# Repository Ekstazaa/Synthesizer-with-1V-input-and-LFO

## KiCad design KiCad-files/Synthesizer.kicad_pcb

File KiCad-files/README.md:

## KiCad Design Files

This folder contains the KiCad design files for the analog synthesizer PCB.

### File descriptions

- **Synthesizer.kicad_sch**  
  KiCad schematic file containing the complete circuit design, including the VCO, exponential converter, summing amplifier, LFO, and supporting circuitry.

- **Synthesizer.kicad_pcb**  
  KiCad PCB layout file defining the board outline, component placement, routing, and copper layers.

- **Synthesizer.kicad_pro**  
  KiCad project file that links the schematic and PCB layout and stores project-specific settings.

- **Synthesizer_fab_file_11_01_26.zip**  
  Fabrication files exported from KiCad, including Gerber files and drill data, ready for PCB manufacturing.

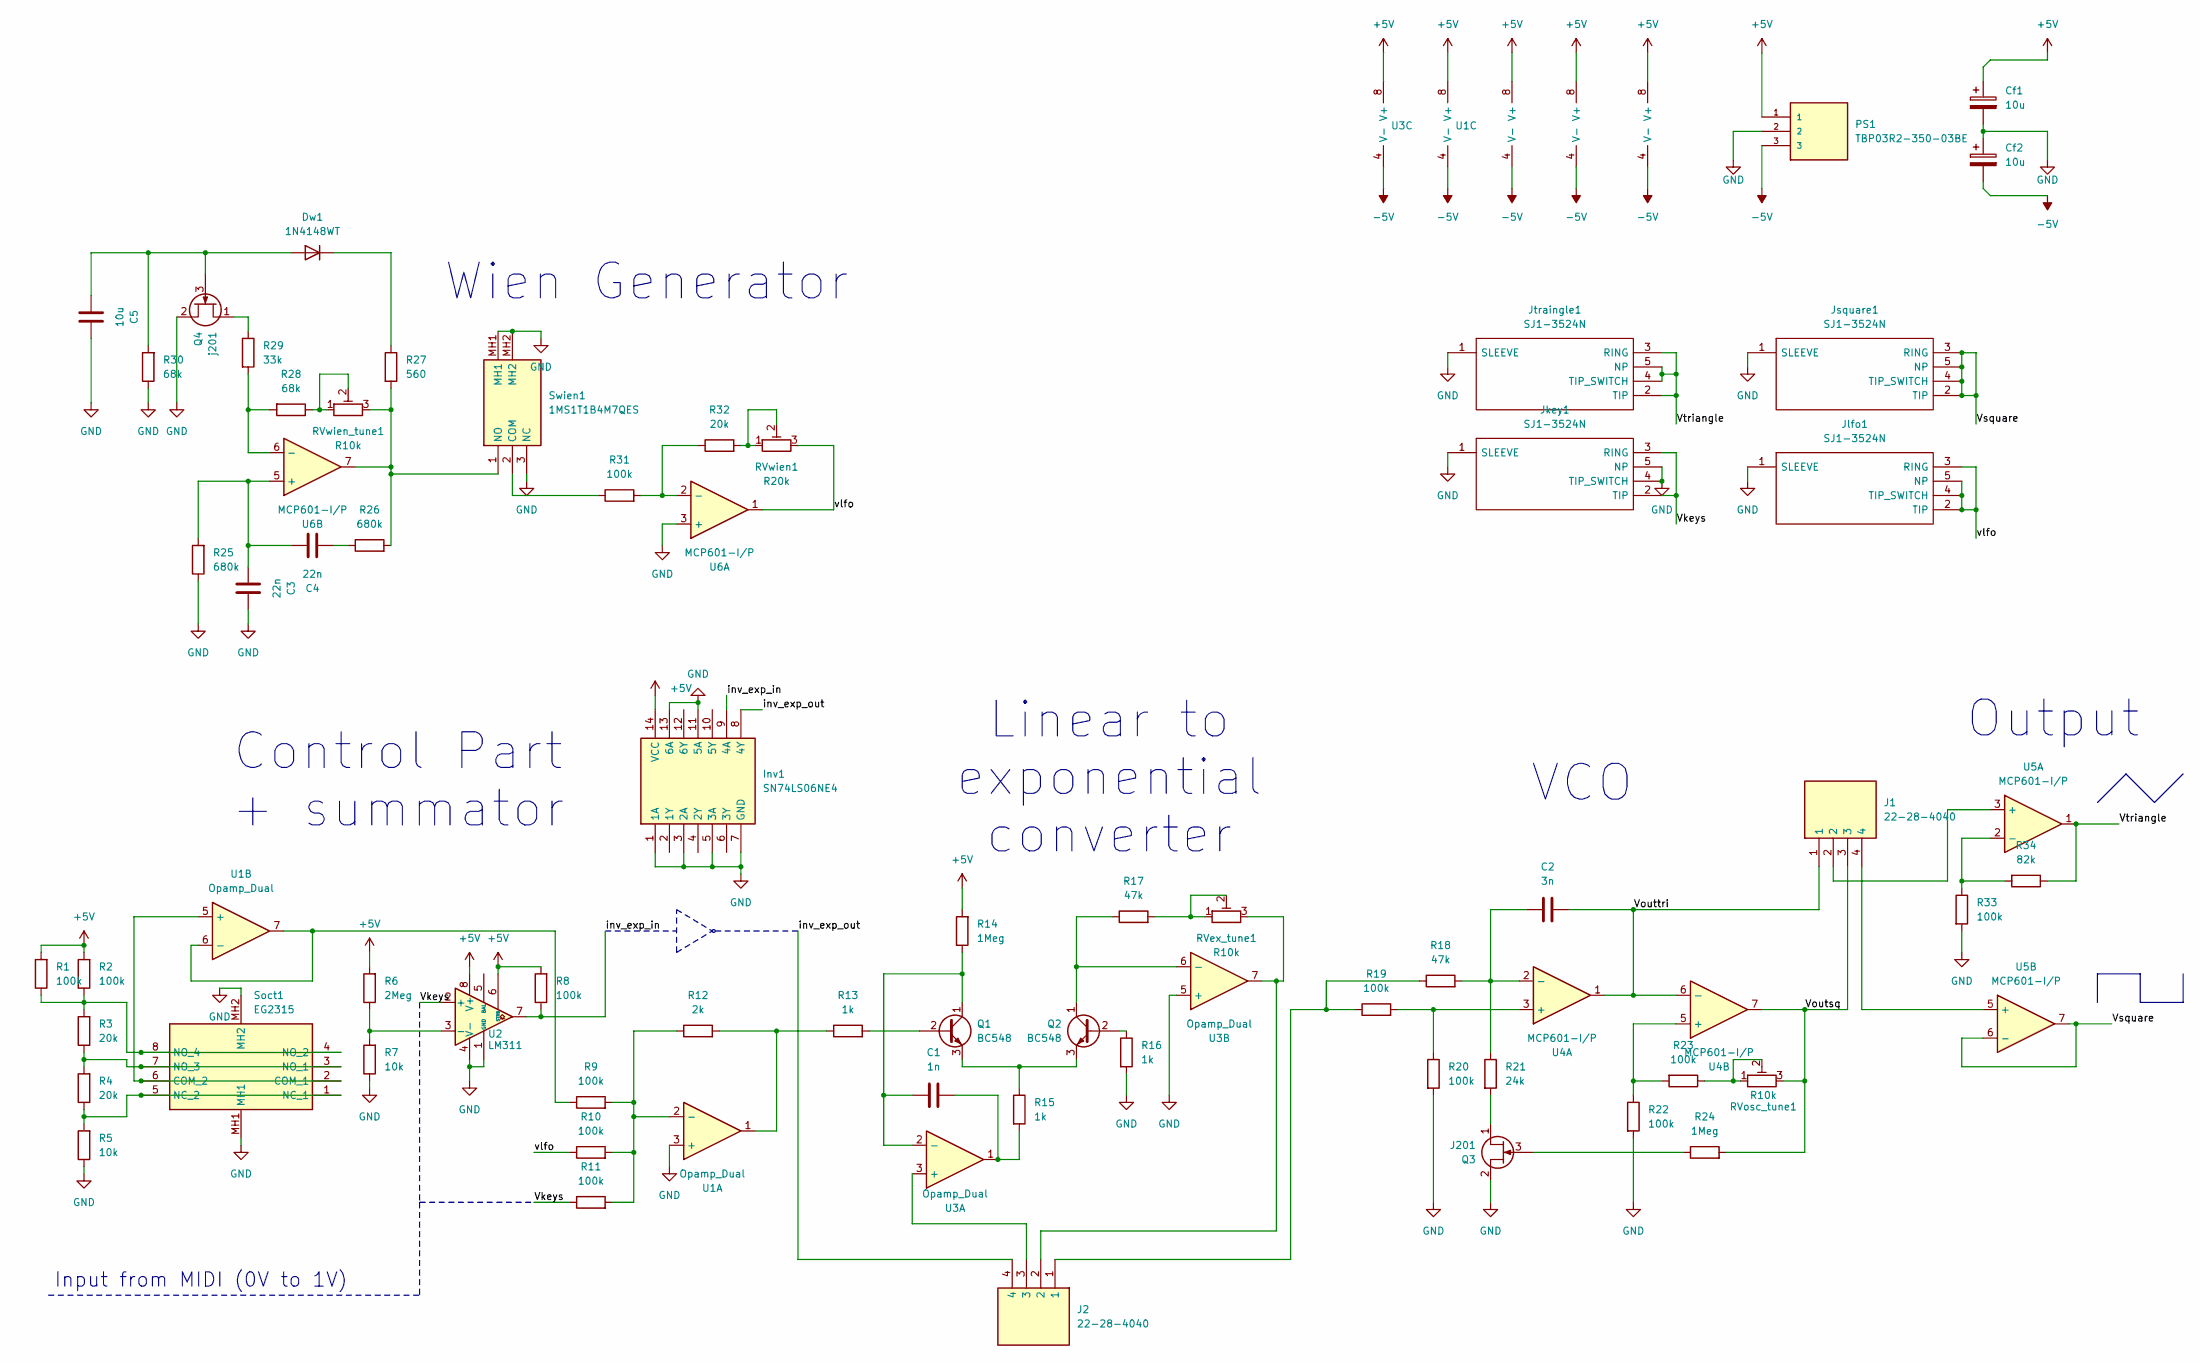
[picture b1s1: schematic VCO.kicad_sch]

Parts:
C1: 1n; C_0805_2012Metric
C2: 3n; C_0805_2012Metric; Tolerance 1%
C3, C4: 22n; C_0805_2012Metric
C5: 10u; C_0805_2012Metric
Cf1, Cf2: 10u; CP_Radial_Tantal_D4.5mm_P2.50mm
Dw1: 1N4148WT; D_SOD-523
Inv1: SN74LS06NE4; DIP794W53P254L1930H508Q14N; Mouser Part Number 595-SN74LS06NE4
J1, J2: 22-28-4040; HDRV4W66P0X254_1X4_1016X249X838P; Manufacturer_Part_Number 22-28-4040
Jkey1: SJ1-3524N; SJ13524N; Mouser Part Number 490-SJ1-3524N
Jlfo1: SJ1-3524N; SJ13524N; Mouser Part Number 490-SJ1-3524N
Jsquare1: SJ1-3524N; SJ13524N; Mouser Part Number 490-SJ1-3524N
Jtraingle1: SJ1-3524N; SJ13524N; Mouser Part Number 490-SJ1-3524N
PS1: TBP03R2-350-03BE; CUI_TBP03R2-350-03BE; PARTREV 1.0
Q1, Q2: BC548; TO-92_Inline
Q3: J201; TO-92_Inline
Q4: j201; TO-92_Inline
R1, R2, R8, R9, R10, R11, R19, R20, R22, R23, R31, R33: 100k; R_0603_1608Metric; Tolerance 1%
R3, R4, R32: 20k; R_0603_1608Metric; Tolerance 1%
R5, R7: 10k; R_0603_1608Metric; Tolerance 1%
R6: 2Meg; R_0603_1608Metric; Tolerance 1%
R12: 2k; R_0603_1608Metric; Tolerance 1%
R13, R15, R16: 1k; R_0603_1608Metric; Tolerance 1%
R14, R24: 1Meg; R_0603_1608Metric; Tolerance 1%
R17, R18: 47k; R_0603_1608Metric; Tolerance 1%
R21: 24k; R_0603_1608Metric; Tolerance 1%
R25, R26: 680k; R_0603_1608Metric; Tolerance 1%
R27: 560; R_0603_1608Metric; Tolerance 1%
R28, R30: 68k; R_0603_1608Metric; Tolerance 1%
R29: 33k; R_0603_1608Metric; Tolerance 1%
R34: 82k; R_0603_1608Metric; Tolerance 1%
RVex_tune1: R10k; Potentiometer_ACP_CA9-H5_Horizontal
RVosc_tune1: R10k; Potentiometer_ACP_CA9-H5_Horizontal
RVwien1: R20k; Potentiometer_Alps_RK163_Single_Horizontal
RVwien_tune1: R10k; Potentiometer_ACP_CA9-H5_Horizontal
Soct1: EG2315; Manufacturer_Part_Number EG2315
Swien1: 1MS1T1B4M7QES; Mouser Part Number 118-1MS1T1B4M7QES
U1, U3: Opamp_Dual; DIP-8_W7.62mm
U2: LM311; DIP-8_W7.62mm
U4, U5, U6: MCP601-I/P; DIP-8_W7.62mm

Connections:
+5V: Cf1.1, Inv1.14 (VCC), PS1.1, R1.2, R2.2, R6.2, R8.2, R14.2, U1.8 (V+), U2.6 (STRB), U2.8 (V+), U3.8 (V+), U4.8 (V+), U5.8 (V+), U6.8 (V+)
-5V: Cf2.2, PS1.3, U1.4 (V-), U3.4 (V-), U4.4 (V-), U5.4 (V-), U6.4 (V-)
/Vkeys: Jkey1.2 (TIP), Jkey1.3 (RING), R11.1, U2.2 (+)
/Voutsq: J1.3, R24.2, RVosc_tune1.3, U4.7
/Vouttri: C2.2, J1.1, U4.1, U4.6 (-)
/Vsquare: Jsquare1.2 (TIP), Jsquare1.3 (RING), Jsquare1.4 (TIP_SWITCH), Jsquare1.5 (NP), U5.6 (-), U5.7
/Vtriangle: Jtraingle1.2 (TIP), Jtraingle1.3 (RING), Jtraingle1.4 (TIP_SWITCH), Jtraingle1.5 (NP), R34.1, U5.1
/inv_exp_in: Inv1.9 (4A), R8.1, U2.7
/inv_exp_out: Inv1.8 (4Y), J2.4
/vlfo: Jlfo1.2 (TIP), Jlfo1.3 (RING), Jlfo1.4 (TIP_SWITCH), Jlfo1.5 (NP), R10.1, RVwien1.3, U6.1
GND: C3.2, C5.2, Cf1.2, Cf2.1, Inv1.1 (1A), Inv1.3 (2A), Inv1.5 (3A), Inv1.7 (GND), Inv1.11 (5A), Inv1.13 (6A), Jkey1.1 (SLEEVE), Jkey1.4 (TIP_SWITCH), Jkey1.5 (NP), Jlfo1.1 (SLEEVE), Jsquare1.1 (SLEEVE), Jtraingle1.1 (SLEEVE), PS1.2, Q3.2 (S), Q4.2 (S), R5.1, R7.1, R16.2, R20.2, R22.2, R25.1, R30.1, R33.2, Soct1.MH1, Soct1.MH2, Swien1.3 (NC), Swien1.MH1, Swien1.MH2, U1.3 (+), U2.1 (GND), U2.4 (V-), U3.5 (+), U6.3 (+)
unnamed: C1.2, R15.2, U3.1
unnamed: C4.1, R26.1
unnamed: C5.1, Dw1.2 (A), Q4.3 (G), R30.2
unnamed: Dw1.1 (K), R27.1
unnamed: J2.1, R18.1, R19.1
unnamed: J2.2, RVex_tune1.3, U3.7
unnamed: Q1.2 (B), R13.2
unnamed: C1.1, Q1.1 (C), R14.1, U3.2 (-)
unnamed: Q1.3 (E), Q2.3 (E), R15.1
unnamed: Q2.2 (B), R16.1
unnamed: Q2.1 (C), R17.1, U3.6 (-)
unnamed: Q3.1 (D), R21.2
unnamed: Q3.3 (G), R24.1
unnamed: Q4.1 (D), R29.1
unnamed: R12.2, R13.1, U1.1
unnamed: R17.2, RVex_tune1.1, RVex_tune1.2
unnamed: R23.1, RVosc_tune1.1, RVosc_tune1.2
unnamed: R28.1, RVwien_tune1.1, RVwien_tune1.2
unnamed: R32.2, RVwien1.1, RVwien1.2
unnamed: Soct1.2 (COM_1), Soct1.6 (COM_2), U1.5 (+)
unnamed: R4.1, R5.2, Soct1.1 (NC_1), Soct1.5 (NC_2)
unnamed: R3.1, R4.2, Soct1.3 (NO_1), Soct1.7 (NO_3)
unnamed: R1.1, R2.1, R3.2, Soct1.4 (NO_2), Soct1.8 (NO_4)
unnamed: R31.1, Swien1.2 (COM)
unnamed: R26.2, R27.2, RVwien_tune1.3, Swien1.1 (NO), U6.7
unnamed: R9.2, R10.2, R11.2, R12.1, U1.2 (-)
unnamed: R9.1, U1.6 (-), U1.7
unnamed: R6.1, R7.2, U2.3 (-)
unnamed: J2.3, U3.3 (+)
unnamed: R19.2, R20.1, U4.3 (+)
unnamed: C2.1, R18.2, R21.1, U4.2 (-)
unnamed: R22.1, R23.2, U4.5 (+)
unnamed: J1.2, U5.3 (+)
unnamed: R33.1, R34.2, U5.2 (-)
unnamed: J1.4, U5.5 (+)
unnamed: R31.2, R32.1, U6.2 (-)
unnamed: C3.1, C4.2, R25.2, U6.5 (+)
unnamed: R28.2, R29.2, U6.6 (-)

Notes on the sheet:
Output
Linear to exponential converter
Input from MIDI (0V to 1V)
Control Part + summator
Wien Generator
VCO

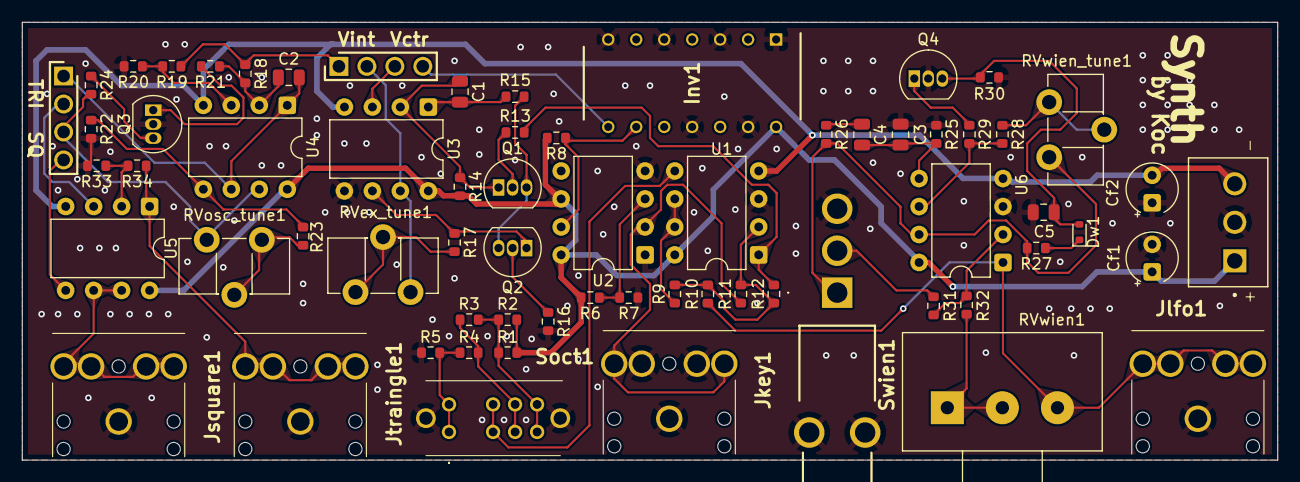
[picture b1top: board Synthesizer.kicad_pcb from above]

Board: 2 copper layers, 114.0 x 39.8 mm, 66 parts (0 on the bottom side), 49 nets.

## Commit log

2026-01-29 Rename VCO.kicad_pro to Synthesizer.kicad_pro
2026-01-29 Rename vco_lay_11_01_26.zip to Synthesizer_fab_file_11_01_26.zip
